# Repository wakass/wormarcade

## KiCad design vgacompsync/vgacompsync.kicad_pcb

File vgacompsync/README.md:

A small kicad project for a VGA to RGB-composite adapter.

From [here](https://www.epanorama.net/circuits/vga2rgbs.html)

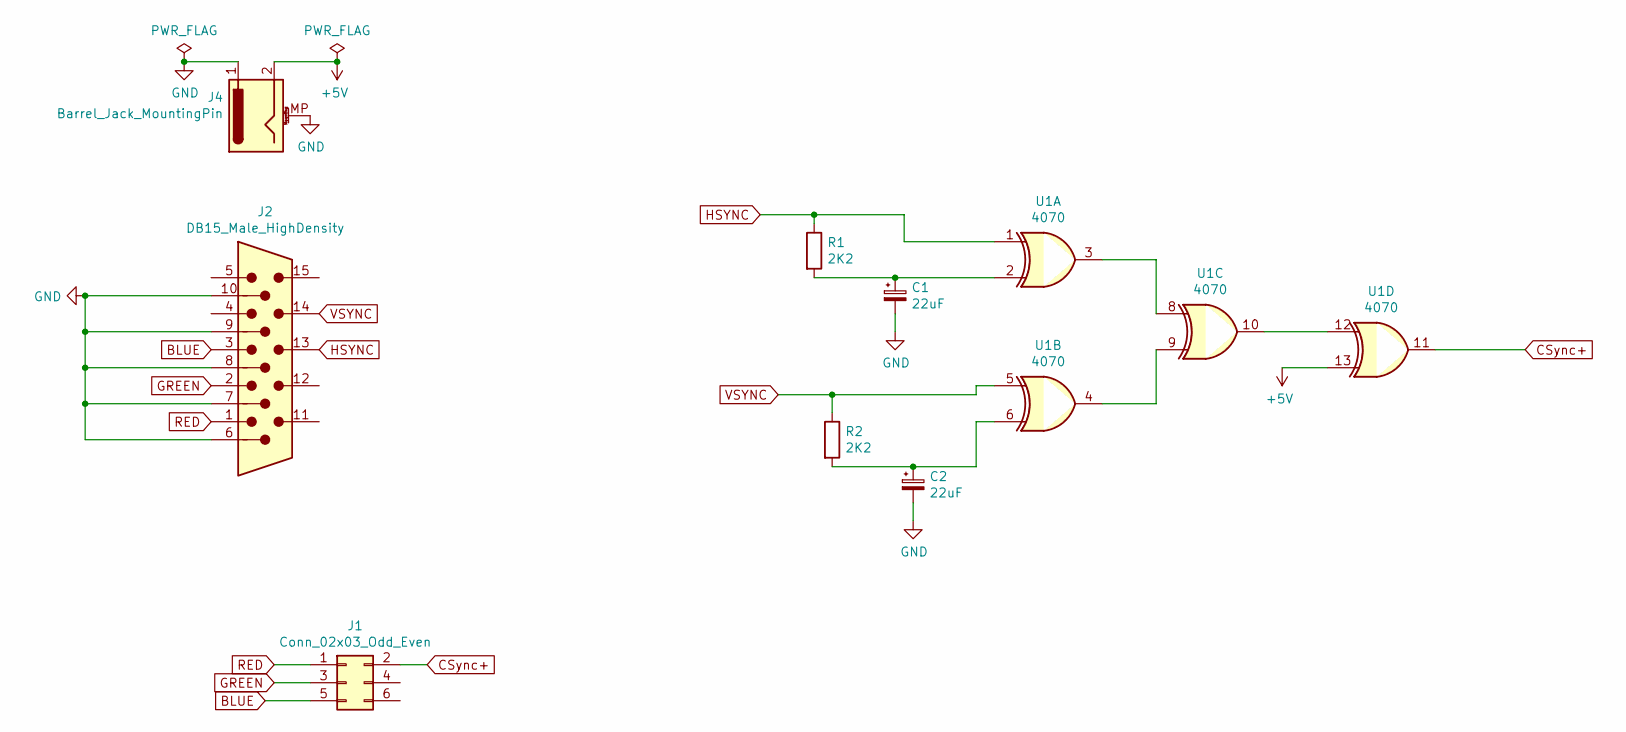
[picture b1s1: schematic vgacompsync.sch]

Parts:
C1, C2: 22uF; CP_Radial_D4.0mm_P1.50mm
J1: Conn_02x03_Odd_Even; PinHeader_2x03_P2.54mm_Vertical
J2: DB15_Male_HighDensity; DSUB-15-HD_Male_Horizontal_P2.29x1.98mm_EdgePinOffset3.03mm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
J4: Barrel_Jack_MountingPin; BarrelJack_CUI_PJ-063AH_Horizontal
R1, R2: 2K2; R_Axial_DIN0204_L3.6mm_D1.6mm_P1.90mm_Vertical
U1: 4070; DIP-14_W7.62mm

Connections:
+5V: J4.2, U1.13
BLUE: J1.5, J2.3
CSync+: J1.2, U1.11
GND: C1.2, C2.2, J2.6, J2.7, J2.8, J2.9, J2.10, J4.1, J4.MP (MountPin)
GREEN: J1.3, J2.2
HSYNC: J2.13, R1.1, U1.1
unnamed: C1.1, R1.2, U1.2
unnamed: C2.1, R2.2, U1.6
unnamed: U1.3, U1.8
unnamed: U1.4, U1.9
unnamed: U1.10, U1.12
RED: J1.1, J2.1
VSYNC: J2.14, R2.1, U1.5

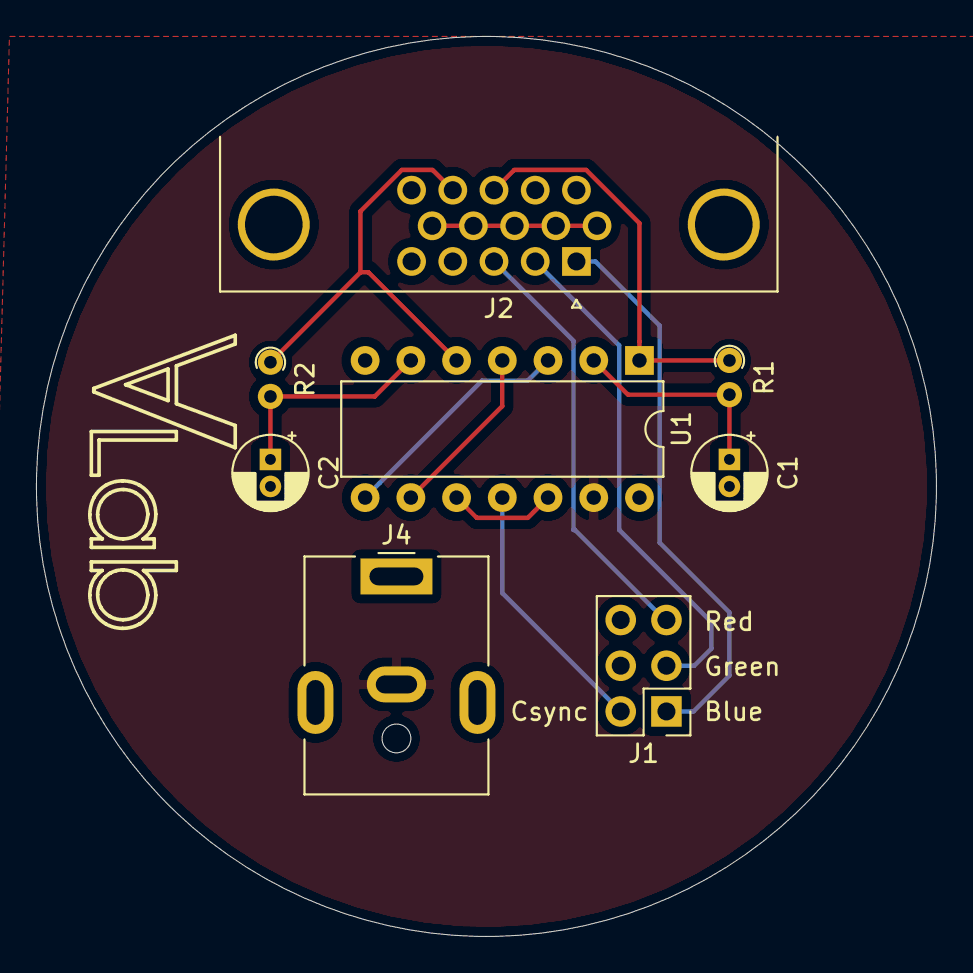
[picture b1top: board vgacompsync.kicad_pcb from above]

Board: 2 copper layers, 50.0 x 50.0 mm, 8 parts (0 on the bottom side), 13 nets.

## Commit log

2021-01-19 Added electrical schematic found on the internet
2021-01-19 Added ultimate mortal kombat 3 control panel cutout in acrylic, as found on the machine. Has weird deviations from centerlines, so this was definitely manually produced along with the cabinet contro 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
2021-01-19 Added ironman super offroad manual
2021-01-24 Added vga to rgb composite sync pcb design
2021-01-24 Added docs: Crt connectors, crt, general notes
2021-02-09 Split general into maintenance and operator part
2021-02-11 Added donation-op documentation
2021-03-17 Added bootleg-pcb elaboration and kickharness design
